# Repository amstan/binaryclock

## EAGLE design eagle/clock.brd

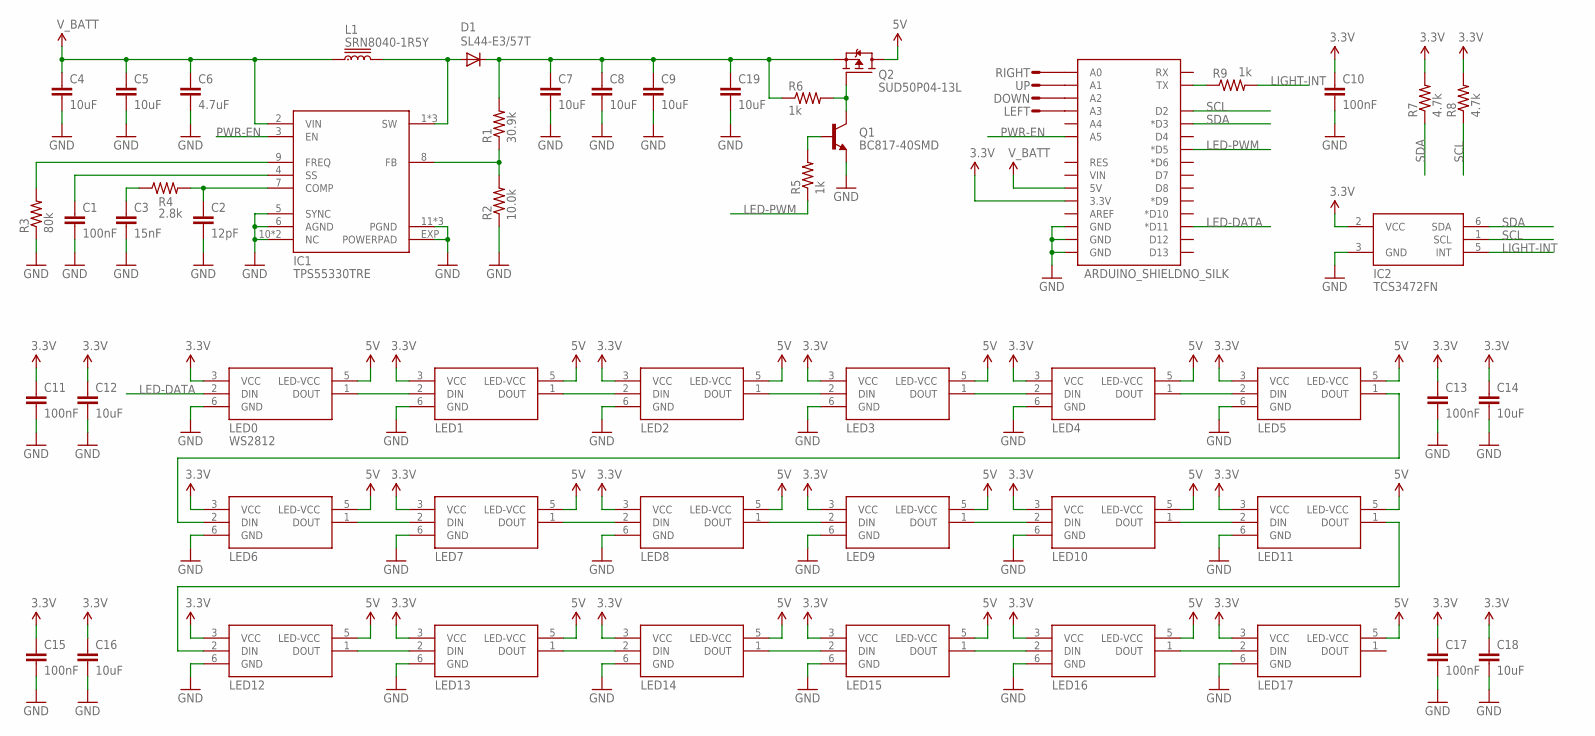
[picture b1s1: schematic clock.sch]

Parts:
C1, C10, C11, C13, C15, C17: 100nF; C0603K
C2: 12pF; C0603K
C3: 15nF; C0603K
C4, C5, C7, C8, C9, C12, C14, C16, C18, C19: 10uF; C1206K
C6: 4.7uF; C0805K
CN1: ARDUINO_SHIELDNO_SILK; DUEMILANOVE_VIAS
D1: SL44-E3/57T; SMC
DOWN: CAP-PAD15MM; CAP-PAD-15MM
IC1: TPS55330TRE; QFN16
IC2: TCS3472FN; DFN-6
L1: SRN8040-1R5Y; SRN8040
LED0, LED1, LED2, LED3, LED4, LED5, LED6, LED7, LED8, LED9, LED10, LED11, LED12, LED13, LED14, LED15, LED16, LED17: WS2812; LED-TRICOLOR-5050-IC
LEFT: CAP-PAD15MM; CAP-PAD-15MM
Q1: BC817-40SMD; SOT23-BEC
Q2: SUD50P04-13L; TO252
R1: 30.9k; R0603
R2: 10.0k; R0603
R3: 80k; R0603
R4: 2.8k; R0603
R5, R6, R9: 1k; R0603
R7, R8: 4.7k; R0603
RIGHT: CAP-PAD15MM; CAP-PAD-15MM
UP: CAP-PAD15MM; CAP-PAD-15MM

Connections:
3.3V: C10.1, C11.1, C12.1, C13.1, C14.1, C15.1, C16.1, C17.1, C18.1, CN1.3.3V, IC2.2 (VCC), LED0.3 (VCC), LED1.3 (VCC), LED2.3 (VCC), LED3.3 (VCC), LED4.3 (VCC), LED5.3 (VCC), LED6.3 (VCC), LED7.3 (VCC), LED8.3 (VCC), LED9.3 (VCC), LED10.3 (VCC), LED11.3 (VCC), LED12.3 (VCC), LED13.3 (VCC), LED14.3 (VCC), LED15.3 (VCC), LED16.3 (VCC), LED17.3 (VCC), R7.2, R8.2
5V: LED0.5 (LED-VCC), LED1.5 (LED-VCC), LED2.5 (LED-VCC), LED3.5 (LED-VCC), LED4.5 (LED-VCC), LED5.5 (LED-VCC), LED6.5 (LED-VCC), LED7.5 (LED-VCC), LED8.5 (LED-VCC), LED9.5 (LED-VCC), LED10.5 (LED-VCC), LED11.5 (LED-VCC), LED12.5 (LED-VCC), LED13.5 (LED-VCC), LED14.5 (LED-VCC), LED15.5 (LED-VCC), LED16.5 (LED-VCC), LED17.5 (LED-VCC), Q2.3 (D)
COMP: C2.1, IC1.7 (COMP), R4.2
FB: IC1.8 (FB), R1.1, R2.2
FREQ: IC1.9 (FREQ), R3.2
GND: C1.2, C2.2, C3.2, C4.2, C5.2, C6.2, C7.2, C8.2, C9.2, C10.2, C11.2, C12.2, C13.2, C14.2, C15.2, C16.2, C17.2, C18.2, C19.2, CN1.GND@0 (GND), CN1.GND@1 (GND), CN1.GND@2 (GND), IC1.5 (SYNC), IC1.6 (AGND), IC1.10 (NC), IC1.11 (PGND), IC1.12 (PGND), IC1.13 (PGND), IC1.14 (NC), IC1.EXP (POWERPAD), IC2.3 (GND), LED0.6 (GND), LED1.6 (GND), LED2.6 (GND), LED3.6 (GND), LED4.6 (GND), LED5.6 (GND), LED6.6 (GND), LED7.6 (GND), LED8.6 (GND), LED9.6 (GND), LED10.6 (GND), LED11.6 (GND), LED12.6 (GND), LED13.6 (GND), LED14.6 (GND), LED15.6 (GND), LED16.6 (GND), LED17.6 (GND), Q1.E, R2.1, R3.1
LED12: LED12.1 (DOUT), LED13.2 (DIN)
LED15: LED14.1 (DOUT), LED15.2 (DIN)
LED-DATA: CN1.D11 (*D11), LED0.2 (DIN)
LED-PWM: CN1.D5 (*D5), R5.1
LIGHT-INT: IC2.5 (INT), R9.2
unnamed: CN1.A3, LEFT.P$1
unnamed: CN1.A2, DOWN.P$1
unnamed: CN1.A1, UP.P$1
unnamed: CN1.A0, RIGHT.P$1
unnamed: LED0.1 (DOUT), LED1.2 (DIN)
unnamed: CN1.TX, R9.1
unnamed: C3.1, R4.1
unnamed: Q1.B, R5.2
unnamed: Q1.C, Q2.1 (G), R6.2
unnamed: LED1.1 (DOUT), LED2.2 (DIN)
unnamed: LED2.1 (DOUT), LED3.2 (DIN)
unnamed: LED3.1 (DOUT), LED4.2 (DIN)
unnamed: LED4.1 (DOUT), LED5.2 (DIN)
unnamed: LED6.1 (DOUT), LED7.2 (DIN)
unnamed: LED7.1 (DOUT), LED8.2 (DIN)
unnamed: LED8.1 (DOUT), LED9.2 (DIN)
unnamed: LED9.1 (DOUT), LED10.2 (DIN)
unnamed: LED10.1 (DOUT), LED11.2 (DIN)
unnamed: LED5.1 (DOUT), LED6.2 (DIN)
unnamed: LED13.1 (DOUT), LED14.2 (DIN)
unnamed: LED15.1 (DOUT), LED16.2 (DIN)
unnamed: LED16.1 (DOUT), LED17.2 (DIN)
unnamed: LED11.1 (DOUT), LED12.2 (DIN)
PWR-EN: CN1.A5, IC1.3 (EN)
SCL: CN1.D2, IC2.1 (SCL), R8.1
SDA: CN1.D3 (*D3), IC2.6 (SDA), R7.1
SMPSU-OUTPUT: C7.1, C8.1, C9.1, C19.1, D1.C, Q2.2 (S), R1.2, R6.1
SS: C1.1, IC1.4 (SS)
SW: D1.A, IC1.1 (SW), IC1.15 (SW), IC1.16 (SW), L1.P$2 (2)
V_BATT: C4.1, C5.1, C6.1, CN1.5V, IC1.2 (VIN), L1.P$1 (1)

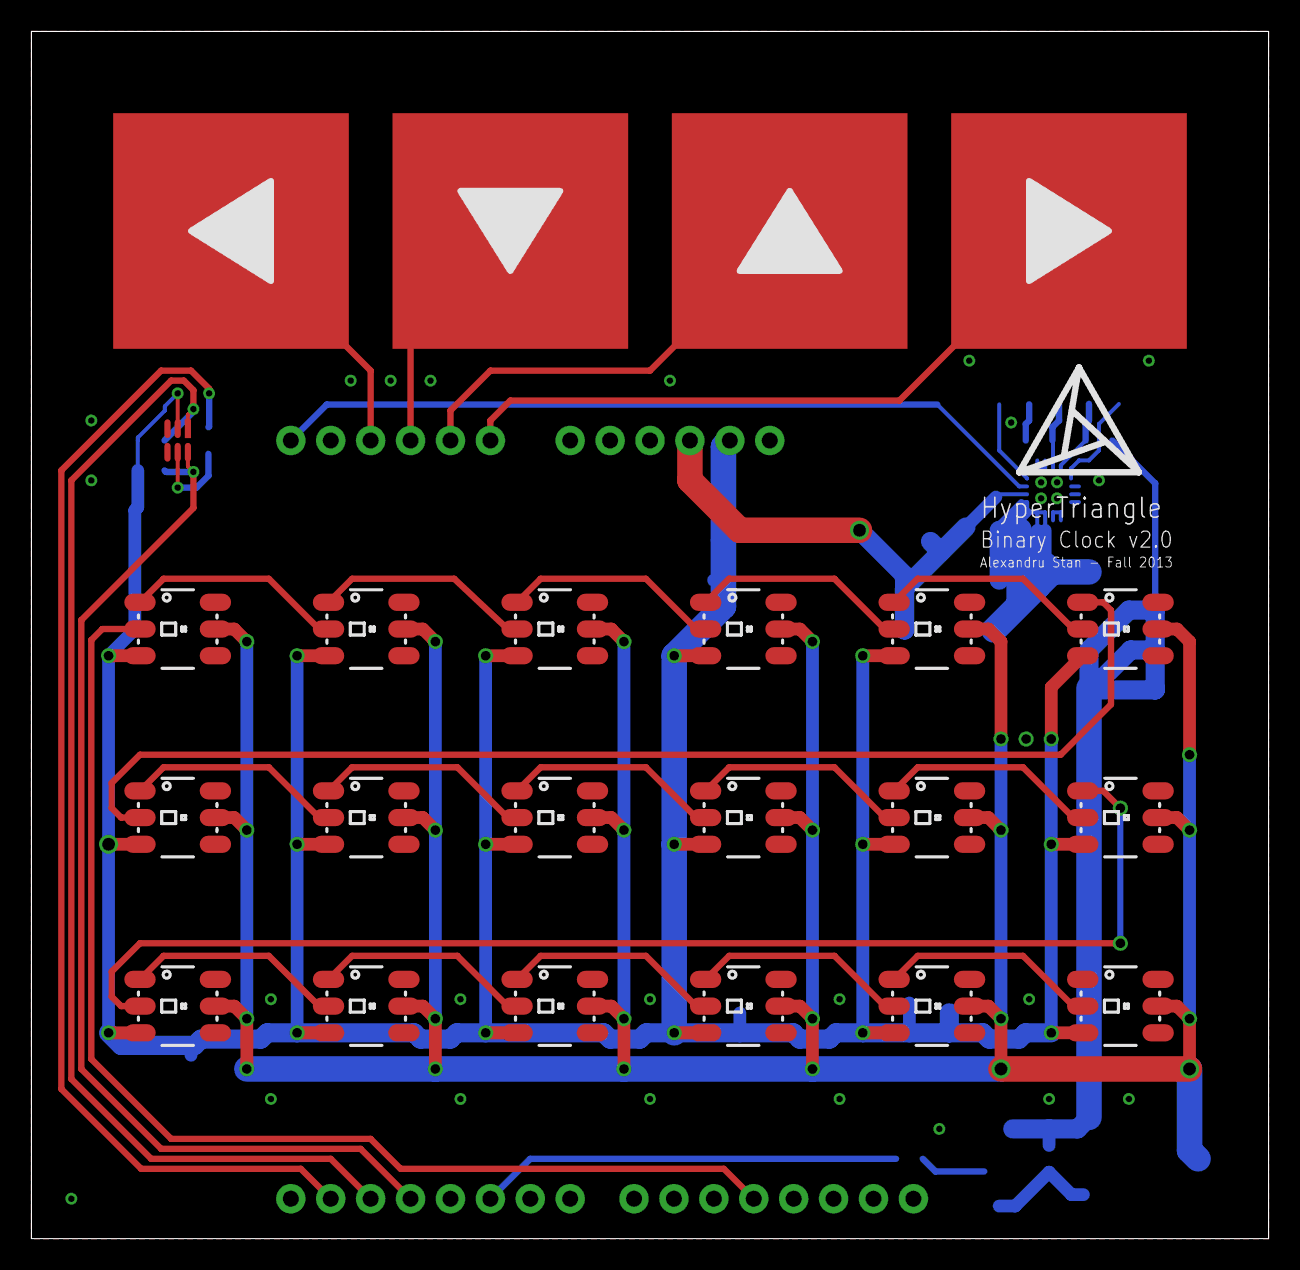
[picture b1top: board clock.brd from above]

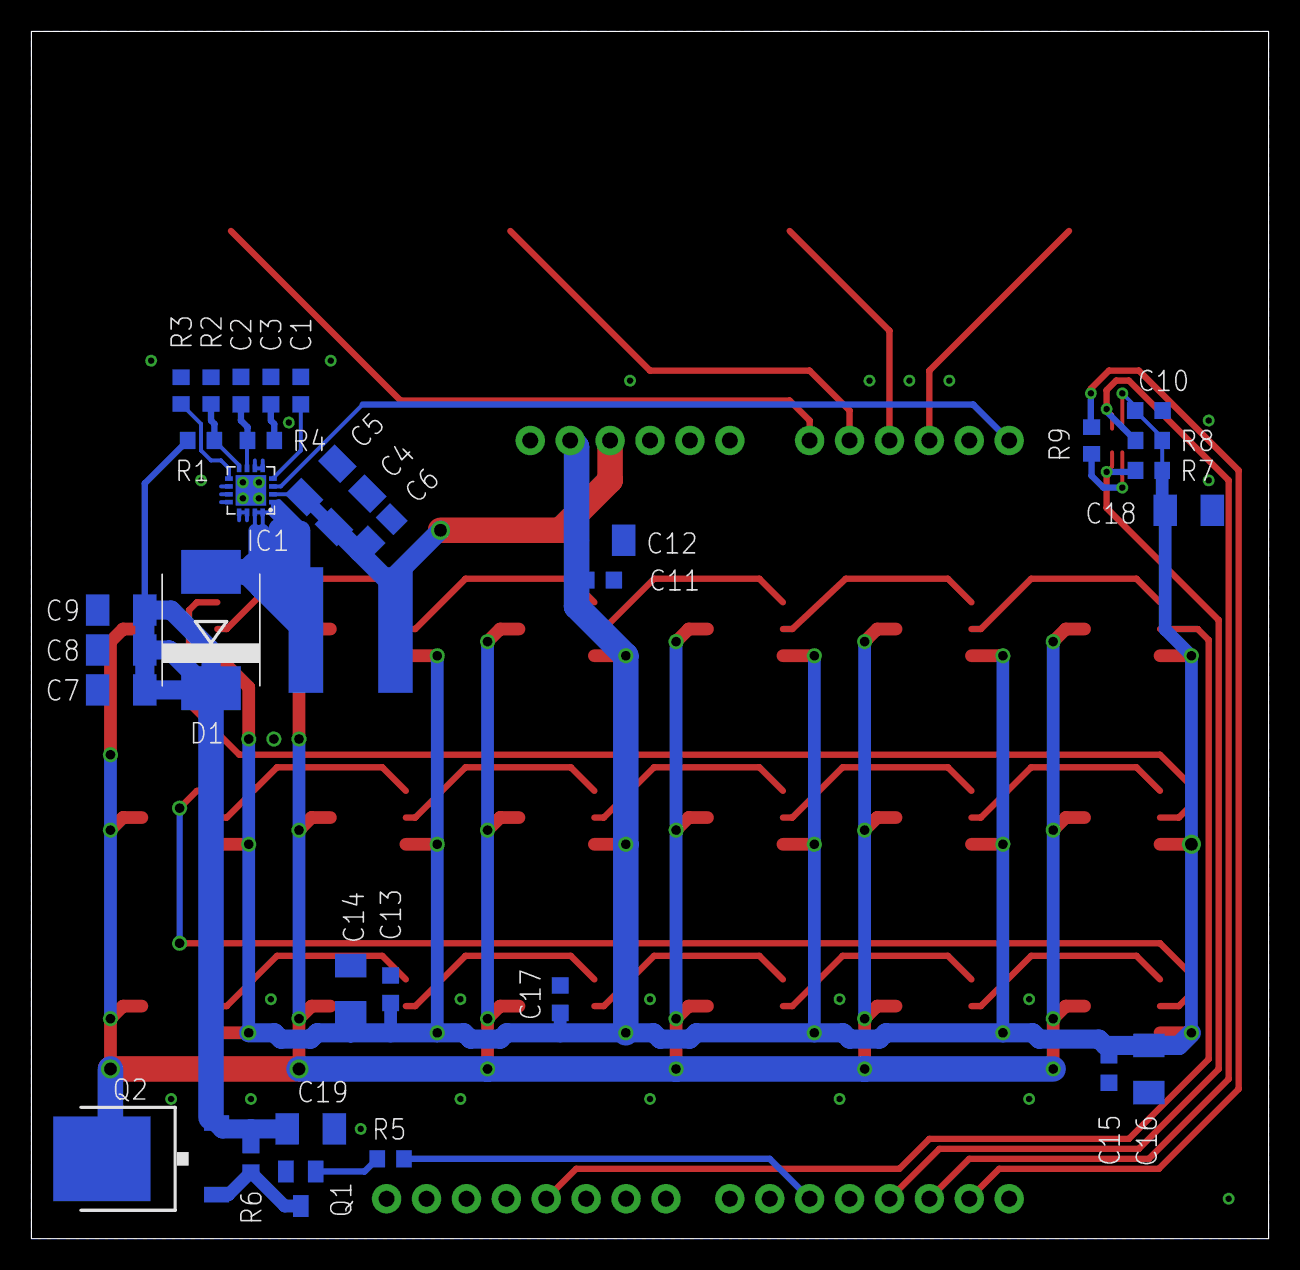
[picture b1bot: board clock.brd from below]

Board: 2 copper layers, 78.7 x 76.8 mm, 57 parts (33 on the bottom side), 41 nets.

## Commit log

2013-10-21 added version 1
2013-10-21 created folder structure
2013-10-21 added pdfs
2013-10-21 Redesigned schematic. Moved from upverter.
2013-10-22 started work on the layout. PSU is layed out too
2013-10-22 came up with a better location for the buttons
2013-10-22 Almost finished layout
2013-10-22 Seems like there's a bug with the polyfills in eagle. I gave up and I just used one back plane
2013-10-22 Finished silk screen touches. Ready to order.
2013-10-22 Ready to order
2013-10-22 Added Rickta's library for reference.
2013-10-28 Added more docs
2013-10-28 working usb cdc(standalone library ported from energia) on the msp430f5529 launchpad
2013-10-28 working RTC
2013-11-19 preliminary RGB clock to test the finished board
2013-11-22 It's fading now!
2013-11-23 Organized code, added usb, added capacitive touch(really finicky)
2013-11-23 touch working for sure
2013-11-23 Moved capacitive touch to another timer, implemented LED-PWM(unfortunatelly hardware does not support the high frequencies)
2013-11-23 not having much luck with i2c yet
2013-11-25 ready for presentation, a lot of demo functions are available
2014-03-20 After presentation
2014-03-20 added timesetting

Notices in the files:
parts and their libraries:
HyperTriangle: Copyright HyperTriangle 2010-2011
SparkFun-Boards: Licensing: CC v3.0 Share-Alike You are welcome to use this library for commercial purposes.
